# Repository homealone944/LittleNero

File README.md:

# LittleNero

## About this Project

> **NOTE**: This project is NOT finished

This is my second keyboard from scratch, but my first PCB design

## Features

### MVP Features

- QMK Compatible
- Split, Ortholinear, Columnar Staggered, Thumb Cluster
- Low Profile (Kailh Choc)
- USB-C

### Stretch Features

- [ ] LEDs (Backglow, Per-Key, Status Indicators)
- [ ] Hot swappable
- [ ] Bluetooth
- [ ] Extra pins can be soldered to on PCB for expansion?
- [ ] Display?
- [ ] Encoder?

## Keyboard Inspiration

- [ErgoDox Ez](https://ergodox-ez.com/)
- [GergoPlex](https://www.gboards.ca/product/gergoplex)
- [Corne](https://github.com/foostan/crkbd)

## My Process

1) [Find inspiration](./Links.md#Inspiration)
1) [Design layout of keyboard](./Links.md#keyboard-design)
    - [Little Nero Layout](./LittleNero/Layout.json)
1) [Design PCB with KiCad](./Links.md#pcb-design)
1) Order PCB online
1) Assemble PCB
1) Create Firmware
1) Design Case with Fusion 360

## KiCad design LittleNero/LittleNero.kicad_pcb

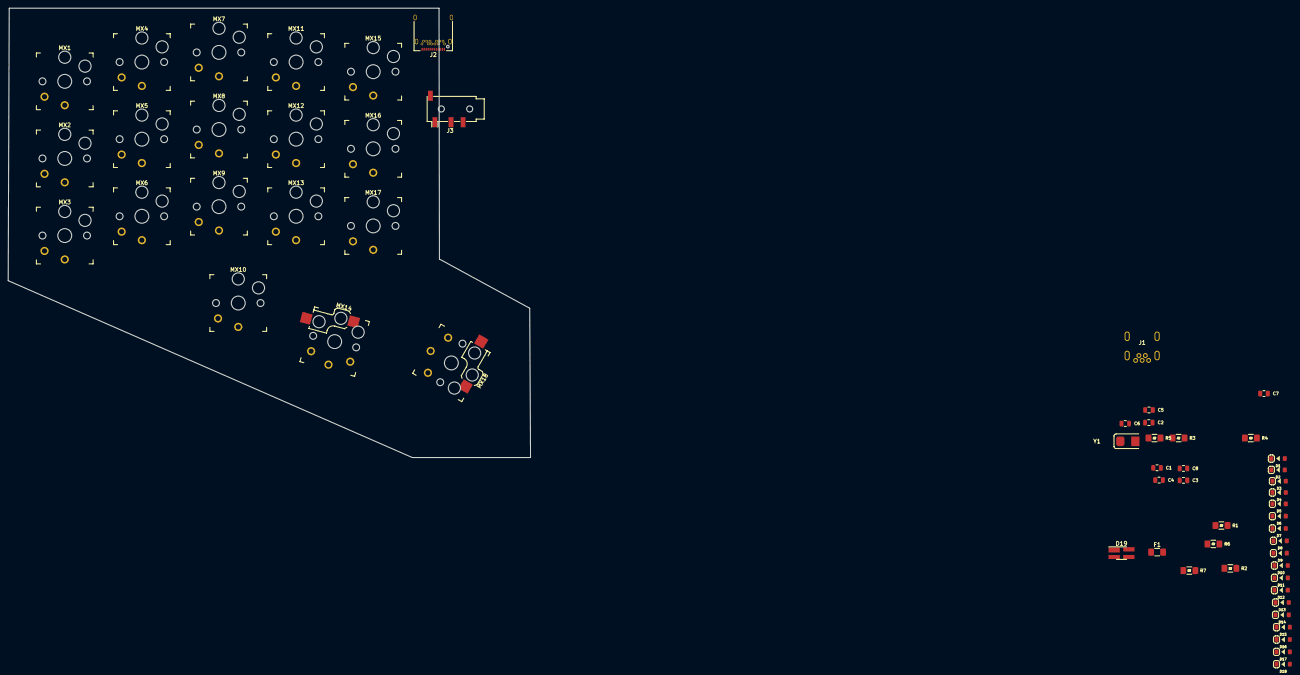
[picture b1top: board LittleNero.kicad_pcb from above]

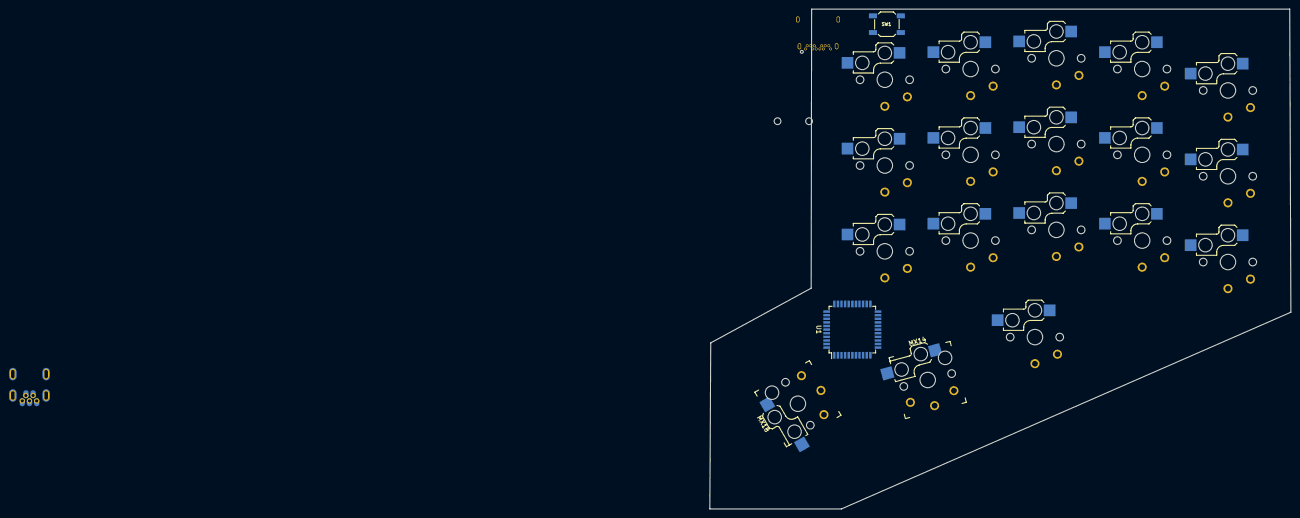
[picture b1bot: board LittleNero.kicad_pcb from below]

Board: 2 copper layers, 129.0 x 111.0 mm, 59 parts (2 on the bottom side), 42 nets, no tracks yet.

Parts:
C1, C2, C3: 22pF; C_0805_2012Metric
C4: 1uF; C_0805_2012Metric
C5: 10uF; C_0805_2012Metric
C6, C7, C8: .1uF; C_0805_2012Metric
D1, D2, D3, D4, D5, D6, D7, D8, D9, D10, D11, D12, D13, D14, D15, D16, D17, D18: 1N4148W; D_SOD-123
D19: PRTR5V0U2X_s; SOT-143_Handsoldering
F1: 500mA; Fuse_1206_3216Metric_Pad1.42x1.75mm_HandSolder
J1: USB_B_Mini; USB_MiniB_XM7D-0512
J2: USB_C_Receptacle; USB_C_Receptacle_Amphenol_12401548E4-2A
J3: AudioJack4; Jack_3.5mm_PJ320D_Horizontal
MX1, MX2, MX3, MX4, MX5, MX6, MX7, MX8, MX9, MX10, MX11, MX12, MX13, MX15, MX16, MX17: mechSwitch; Kailh_socket_PG1350_optional
MX14: mechSwitch; Kailh_socket_PG1350_optional_reversible_1.5
MX18: mechSwitch; Kailh_socket_PG1350_optional_reversible_2
R1, R2: 5k; R_SMD_1206
R3, R5: 10k; R_SMD_1206
R4: 330; R_SMD_1206
R6, R7: 22; R_SMD_1206
SW1: SW_push; K2-1187SQ-A4SW-06
U1: ATmega32U4-AU; TQFP-44_10x10mm_P0.8mm
Y1: 16MHz; Crystal_SMD_5032-2Pin_5.0x3.2mm

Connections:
+5V: C5.2, C6.2, C7.2, C8.2, D19.1, F1.2, J1.1, J2.A1, J2.A12, J2.B1, J2.B12, J2.S1, R1.2, R2.2, R3.2, U1.2, U1.7, U1.14, U1.24, U1.34, U1.44
Col1: MX1.1, MX2.1, MX3.1
Col2: MX4.1, MX5.1, MX6.1
Col3: MX7.1, MX8.1, MX9.1, MX10.1
Col4: MX11.1, MX12.1, MX13.1, MX14.1
Col5: MX15.1, MX16.1, MX17.1, MX18.1
D+: D19.2, J1.3, J2.A6, J2.B6, R6.2
D-: D19.3, J1.2, J2.A7, J2.B7, R7.2
GND: C1.2, C2.2, C4.2, C5.1, C6.1, C7.1, C8.1, J1.5, J3.S, R4.1, R5.1, U1.5, U1.15, U1.23, U1.35, U1.43
unnamed: C1.1, U1.17, Y1.1
unnamed: C2.1, U1.16, Y1.2
unnamed: C3.1, R4.2, SW1.1
unnamed: C4.1, U1.6
unnamed: D1.2, MX1.2
unnamed: D2.2, MX2.2
unnamed: D3.2, MX3.2
unnamed: D4.2, MX4.2
unnamed: D5.2, MX5.2
unnamed: D6.2, MX6.2
unnamed: D7.2, MX7.2
unnamed: D8.2, MX8.2
unnamed: D9.2, MX9.2
unnamed: D10.2, MX10.2
unnamed: D11.2, MX11.2
unnamed: D12.2, MX12.2
unnamed: D13.2, MX13.2
unnamed: D14.2, MX14.2
unnamed: D15.2, MX15.2
unnamed: D16.2, MX16.2
unnamed: D17.2, MX17.2
unnamed: D18.2, MX18.2
unnamed: J2.A5, R1.1
unnamed: J2.B5, R2.1
unnamed: R5.2, U1.33
unnamed: R6.1, U1.4
unnamed: R7.1, U1.3
RST: C3.2, R3.1, SW1.2, U1.13
Row1: D1.1, D4.1, D7.1, D11.1, D15.1
Row2: D2.1, D5.1, D8.1, D12.1, D16.1
Row3: D3.1, D6.1, D9.1, D13.1, D17.1
Row4: D10.1, D14.1, D18.1
VCC: D19.4, F1.1, J2.A4, J2.A9, J2.B4, J2.B9

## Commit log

2021-07-16 Basic Info + Layout + Images + Links
2021-07-16 add more links + cleanup readme
2021-07-16 add KiCad Libs + new KiCad Project
2021-07-16 create schematic + pcb
2021-07-17 add GitIgnore + remove backup files
2021-07-17 add all Rows + Cols
2021-07-17 add image of layout
2021-07-17 update library to show how much space key takes up + add 1.5 & 2u
2021-07-17 update resources + considerations about stabs
2021-07-17 updated schematic + visual pcb
2021-07-17 more documentation
2021-07-18 more walkthroughs + image of full GP back
2021-07-18 Add USB-C
2021-07-18 consideration: perkey leds
